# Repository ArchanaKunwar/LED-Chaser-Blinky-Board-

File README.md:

# Blinky Board (555 LED Chaser)

my first ever PCB!! its a little board with 10 LEDs that chase each other in a loop, and theres a knob on it so you can change how fast they go. thats it. thats the whole thing. but it works and honestly im so proud of it.

built this for Hack Club Half-life and i went in knowing basically nothing about PCB design so if i can do it you definately can.

---

## how it works
 
NE555 runs in astable mode and just oscillates forever, the speed depends on R1, C1 and the pot. that clock feeds the CD4017 (a decade counter) which moves its output over by one every pulse, 0 through 9 then loops back. put an LED on each output and you get the chase effect.
 
all 10 LED cathodes share ONE 470Ω resistor to ground since only one LED is ever on at a time, so you dont need 10 separate ones. blue LEDs come out a bit dimmer tho cause of higher forward voltage.
 
4017 wiring: VDD to +5V, VSS/CLKEN/RESET to GND, CLK to the 555 output pin 3, Cout unused.

---

## Bill of Materials

19 components total, comes out to about **$5.09** in parts.

| Ref | Qty | Value | Footprint | Link | Unit | Total |
|-----|-----|-------|-----------|------|------|-------|
| C1 | 1 | 1 µF | Capacitor_THT:CP_Radial_D5.0mm_P2.00mm | [LCSC C43342](https://www.lcsc.com/product-detail/C43342.html) | $0.14 | $0.14 |
| C2 | 1 | 0.01 µF | Capacitor_THT:C_Disc_D7.5mm_W2.5mm_P5.00mm | [LCSC C454399](https://www.lcsc.com/product-detail/C454399.html) | $0.17 | $0.17 |
| D1-D10 | 10 | LED | LED_THT:LED_D3.0mm | [LCSC C264302](https://www.lcsc.com/product-detail/C264302.html) | $0.10 | $1.00 |
| J1 | 1 | Conn_01x02_Socket | PinHeader_1x02_P2.54mm_Vertical | [DigiKey 929500-01-02-RK](https://www.digikey.com/en/products/result?keywords=929500-01-02-RK) | $0.10 | $0.10 |
| J2 | 1 | Conn_01x01_Socket | PinHeader_1x01_P2.54mm_Vertical | [DigiKey PRPC001DAAN-RC](https://www.digikey.com/en/products/result?keywords=PRPC001DAAN-RC) | $0.05 | $0.05 |
| R1 | 1 | 1kΩ | R_Axial_DIN0207_L6.3mm_D2.5mm_P7.62mm_Horizontal | [DigiKey CFR-25JR-52-1K](https://www.digikey.com/en/products/detail/yageo/CFR-25JR-52-1K/11974) | $0.05 | $0.05 |
| R2 | 1 | 470Ω | R_Axial_DIN0207_L6.3mm_D2.5mm_P7.62mm_Horizontal | [DigiKey CFR-25JR-52-470R](https://www.digikey.com/en/products/detail/yageo/CFR-25JR-52-470R/11966) | $0.05 | $0.05 |
| RV1 | 1 | 50kΩ | Potentiometer_Vishay_T93YA_Vertical | [LCSC C7061697](https://www.lcsc.com/product-detail/Trimmer-Potentiometers_VISHAY-T93YA503KT20_C7061697.html) | $1.58 | $1.58 |
| U1 | 1 | NE555P | DIP-8_W7.62mm | [LCSC C46749](https://www.lcsc.com/product-detail/Timers-Clocks_NE555P_C46749.html) | $0.56 | $0.56 |
| U2 | 1 | CD4017BE | N16 (DIP-16) | [LCSC C34519](https://www.lcsc.com/product-detail/Counters-Dividers_TI-CD4017BE_C34519.html) | $1.39 | $1.39 |

### cost breakdown

| Part | Cost |
|------|------|
| Component BOM | $5.09 |
| JLCPCB order after coupon| $28.23 |
| **parts + PCB** | **$33.32** |

---

## how to build it

1. order the PCB from JLCPCB using the gerbers in this repo. standard green, 1.6mm, default everything. 5 boards is the minimum
2. order the parts from the links above
3. solder the low stuff first (resistors, then the IC sockets or ICs, then caps, then LEDs, pot last)
4. **WATCH YOUR POLARITY.** C1 is electrolytic so it has a + and a -, and all 10 LEDs have a direction too. the short leg is the cathode. i put one LED in backwards and desoldering it was genuinely worse then all the soldering combined
5. power it with 5V through J1
6. turn the pot and watch it go

if nothing lights up, check RESET and CLKEN are actually grounded, thats usually the problem.

---

## whats in this repo

- the KiCad project files (schematic + PCB)
- gerbers + drill files, ready to send to JLCPCB
- the BOM
- my build journal with all the screenshots and every mistake i made along the way
- images folder

---

## stuff i learned / things that went wrong

- the CD4017 footprint isnt in KiCad by default which is so annoying, had to grab it off Ultra Librarian and import it manually
- using labels instead of drawing wires everywhere made my schematic go from spaghetti to actually readable
- DRC hit me with like 15 errors the first time, mostly clearance stuff where traces were to close together. rerouted with more spacing and it cleaned up
- added a ground plane on the bottom layer, helps with noise and also just looks professional

## Made by
Archana Kunwar   
For hackclub

---

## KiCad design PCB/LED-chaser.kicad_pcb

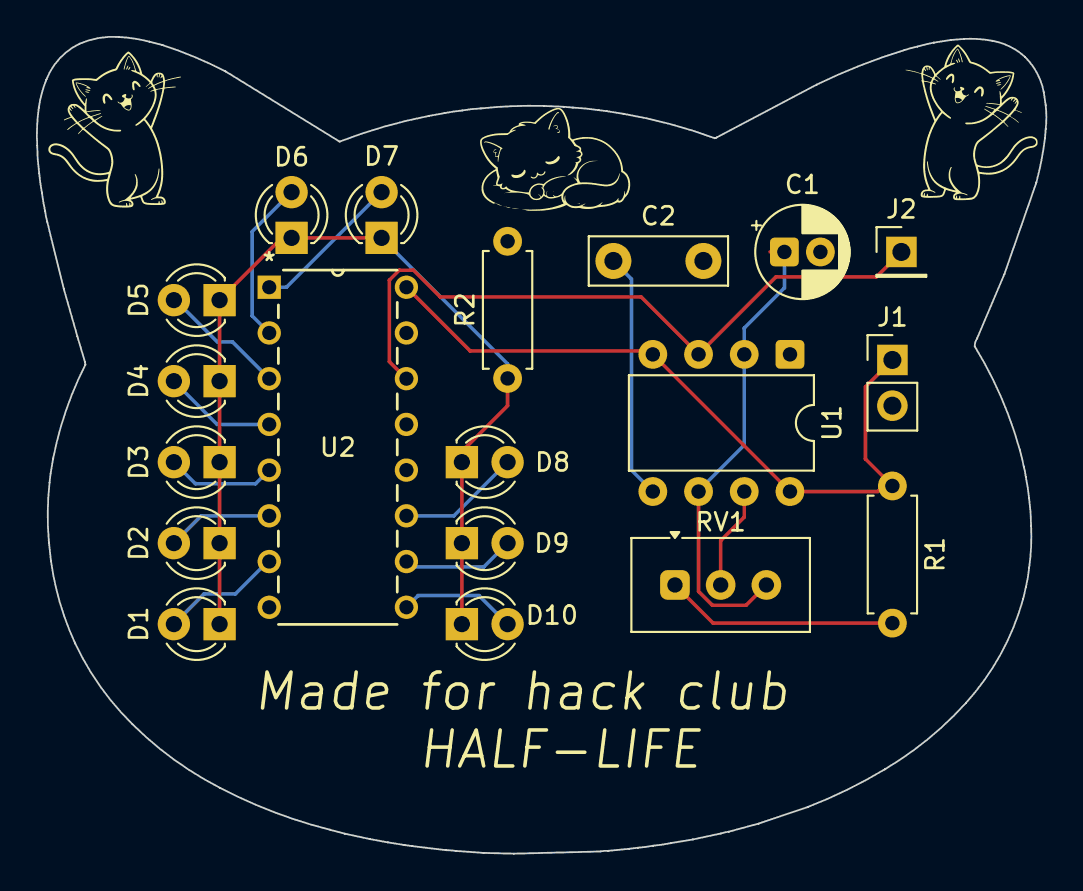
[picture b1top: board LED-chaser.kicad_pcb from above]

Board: 2 copper layers, 56.1 x 45.4 mm, 19 parts (0 on the bottom side), 18 nets.

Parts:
C1: 1 uF; CP_Radial_D5.0mm_P2.00mm
C2: 0.01 uF; C_Disc_D7.5mm_W2.5mm_P5.00mm
D1, D2, D3, D4, D5, D6, D7, D8, D9, D10: LED; LED_D3.0mm
J1: Conn_01x02_Socket; PinHeader_1x02_P2.54mm_Vertical
J2: Conn_01x01_Socket; PinHeader_1x01_P2.54mm_Vertical
R1: 1k; R_Axial_DIN0207_L6.3mm_D2.5mm_P7.62mm_Horizontal
R2: 470; R_Axial_DIN0207_L6.3mm_D2.5mm_P7.62mm_Horizontal
RV1: 50k; Potentiometer_Vishay_T93YA_Vertical
U1: NE555P; DIP-8_W7.62mm
U2: 4017; N16

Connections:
+5V: J1.1, R1.1, U1.4 (~RST), U1.8 (VCC), U2.16 (VDD)
GND: C1.2, C2.2, J1.2, R2.2, U1.1 (GND), U2.8 (VSS), U2.13 (CKEN), U2.15 (Reset)
unnamed: D8.2 (A), U2.11 (Q9)
unnamed: D1.1 (K), D2.1 (K), D3.1 (K), D4.1 (K), D5.1 (K), D6.1 (K), D7.1 (K), D8.1 (K), D9.1 (K), D10.1 (K), R2.1
unnamed: D10.2 (A), U2.9 (Q8)
unnamed: D2.2 (A), U2.6 (Q7)
unnamed: D3.2 (A), U2.5 (Q6)
unnamed: D7.2 (A), U2.1 (Q5)
unnamed: D9.2 (A), U2.10 (Q4)
unnamed: D1.2 (A), U2.7 (Q3)
unnamed: D4.2 (A), U2.4 (Q2)
unnamed: D6.2 (A), U2.2 (Q1)
unnamed: D5.2 (A), U2.3 (Q0)
unnamed: R1.2, RV1.1
unnamed: C2.1, U1.5 (CONT)
unnamed: RV1.2, U1.7 (DISCH)
unnamed: C1.1, RV1.3, U1.2 (TRIG), U1.6 (THRES)
OUT: J2.1 (Pin_1_1), U1.3 (OUT), U2.14 (CLK)
